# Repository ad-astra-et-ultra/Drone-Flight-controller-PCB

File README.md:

# Drone-Flight-controller-PCB
NodeMCU based flight controller PCB for a drone.

## Schematic

## PCB

## 3D VIEW

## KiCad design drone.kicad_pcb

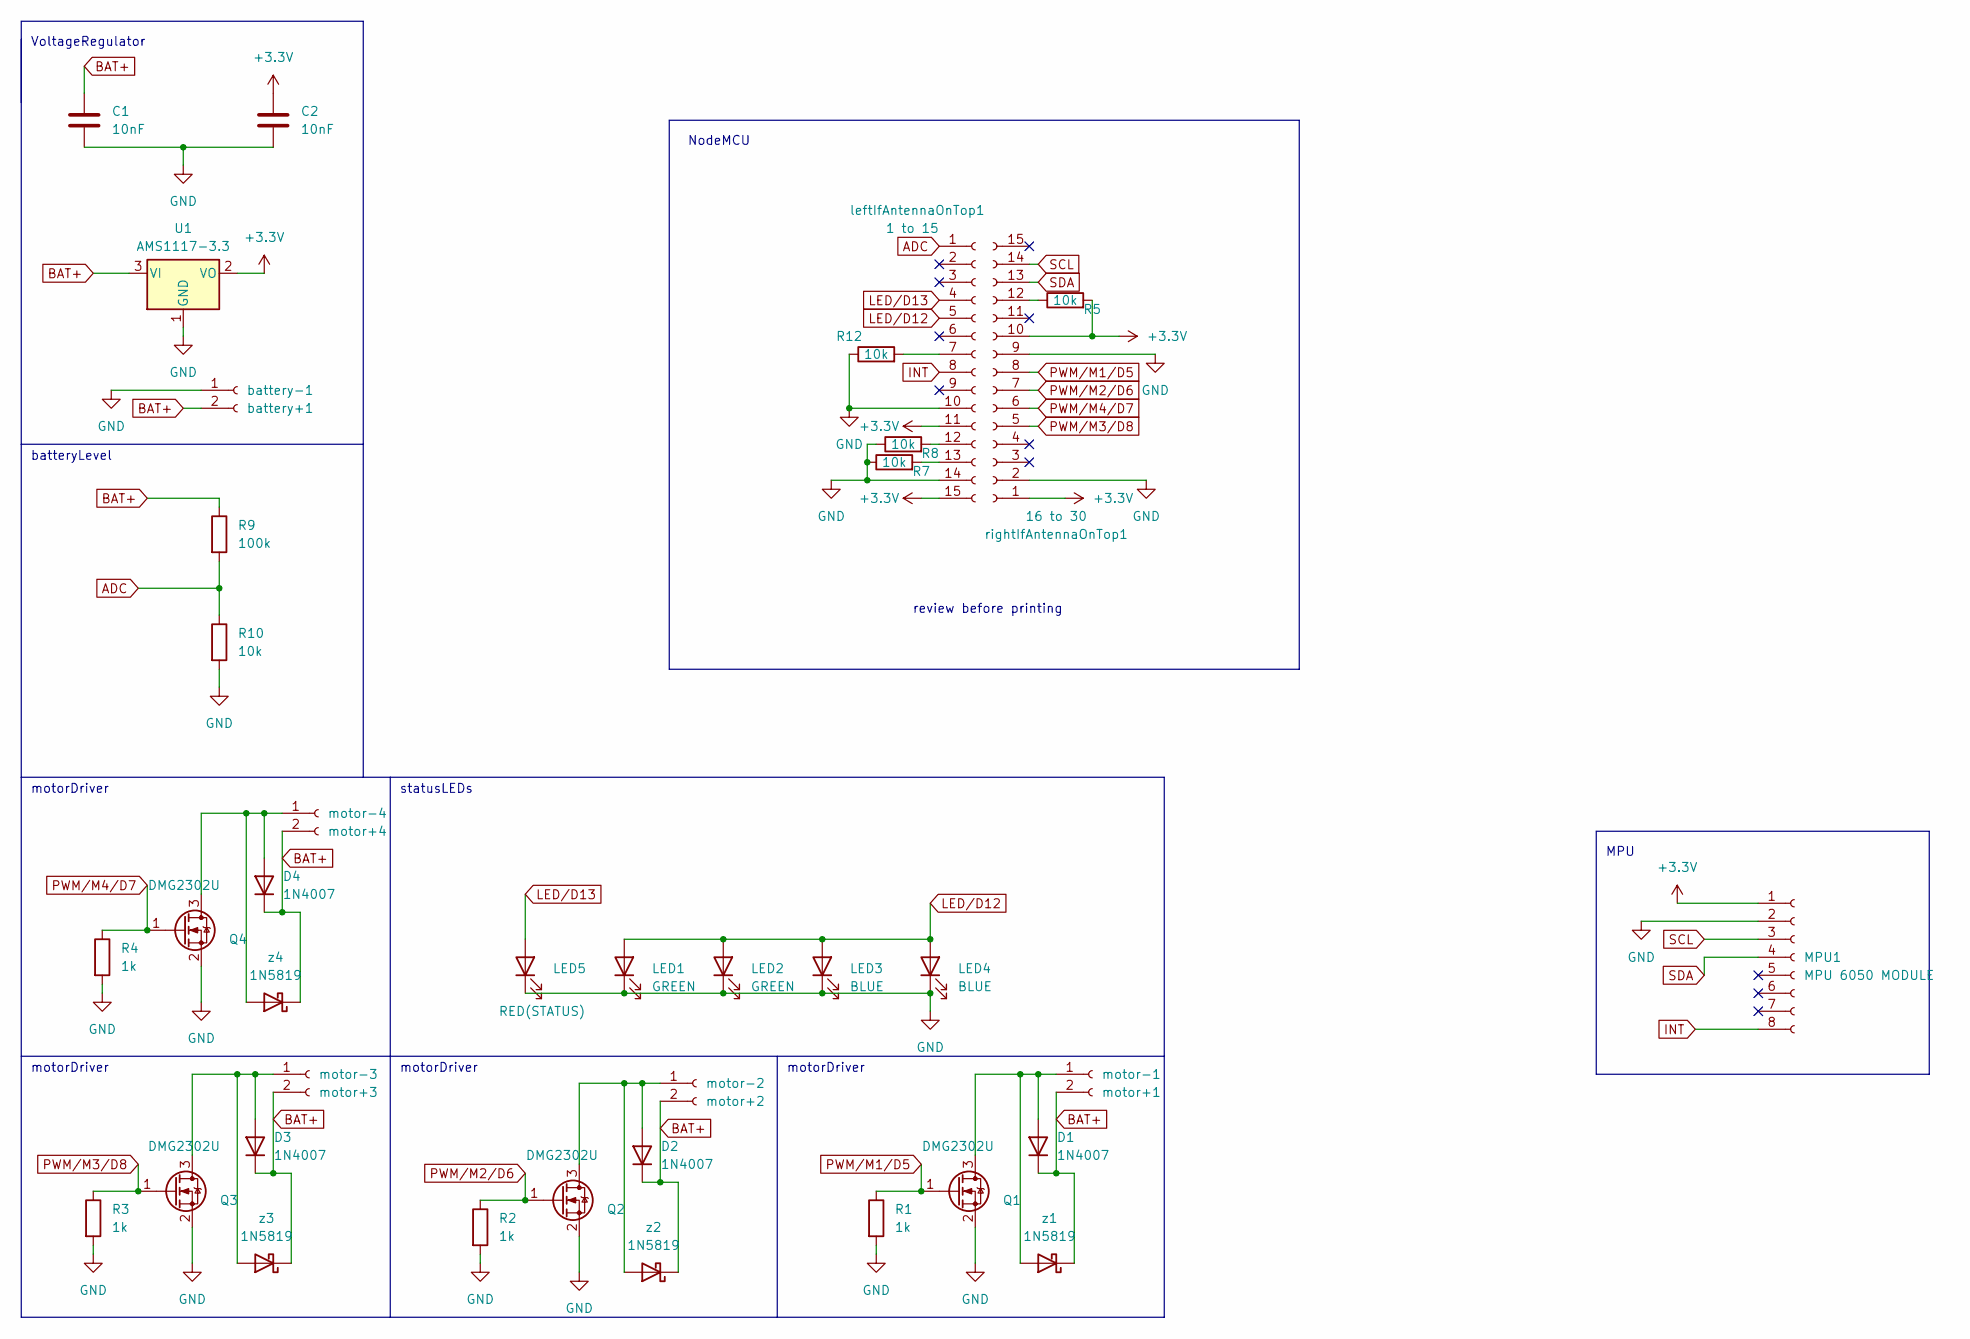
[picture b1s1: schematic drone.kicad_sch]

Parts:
C1, C2: 10nF; C_0201_0603Metric
D1, D2, D3, D4: 1N4007; D_DO-41_SOD81_P10.16mm_Horizontal
LED1, LED2: GREEN; LED_0201_0603Metric
LED3, LED4: BLUE; LED_0201_0603Metric
LED5: RED(STATUS); LED_0201_0603Metric
MPU1: MPU 6050 MODULE; PinSocket_1x08_P2.00mm_Vertical
Q1, Q2, Q3, Q4: DMG2302U; SOT-23
R1, R2, R3, R4: 1k; R_0201_0603Metric
R5, R7, R8, R10, R12: 10k; R_0201_0603Metric
R9: 100k; R_0201_0603Metric
U1: AMS1117-3.3; SOT-223-3_TabPin2
battery-1: battery+1; PinSocket_1x02_P2.00mm_Vertical
leftIfAntennaOnTop1: 1 to 15; PinSocket_1x15_P2.00mm_Vertical
motor-1: motor+1; PinSocket_1x02_P2.00mm_Vertical
motor-2: motor+2; PinSocket_1x02_P2.00mm_Vertical
motor-3: motor+3; PinSocket_1x02_P2.00mm_Vertical
motor-4: motor+4; PinSocket_1x02_P2.00mm_Vertical
rightIfAntennaOnTop1: 16 to 30; PinSocket_1x15_P2.00mm_Vertical
z1, z2, z3, z4: 1N5819; D_DO-41_SOD81_P10.16mm_Horizontal

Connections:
+3V3: C2.1, MPU1.1, R5.2, U1.2 (VO), leftIfAntennaOnTop1.11, leftIfAntennaOnTop1.15, rightIfAntennaOnTop1.1, rightIfAntennaOnTop1.10
ADC: R9.2, R10.1, leftIfAntennaOnTop1.1
BAT+: C1.1, D1.1 (K), D2.1 (K), D3.1 (K), D4.1 (K), R9.1, U1.3 (VI), battery-1.2, motor-1.2, motor-2.2, motor-3.2, motor-4.2, z1.1 (K), z2.1 (K), z3.1 (K), z4.1 (K)
GND: C1.2, C2.2, LED1.1 (K), LED2.1 (K), LED3.1 (K), LED4.1 (K), LED5.1 (K), MPU1.2, Q1.2 (S), Q2.2 (S), Q3.2 (S), Q4.2 (S), R1.2, R2.2, R3.2, R4.2, R7.1, R8.1, R10.2, R12.1, U1.1 (GND), battery-1.1, leftIfAntennaOnTop1.10, leftIfAntennaOnTop1.14, rightIfAntennaOnTop1.2, rightIfAntennaOnTop1.9
INT: MPU1.8, leftIfAntennaOnTop1.8
LED/D12: LED1.2 (A), LED2.2 (A), LED3.2 (A), LED4.2 (A), leftIfAntennaOnTop1.5
LED/D13: LED5.2 (A), leftIfAntennaOnTop1.4
unnamed: D2.2 (A), Q2.3 (D), motor-2.1, z2.2 (A)
unnamed: D3.2 (A), Q3.3 (D), motor-3.1, z3.2 (A)
unnamed: D4.2 (A), Q4.3 (D), motor-4.1, z4.2 (A)
unnamed: D1.2 (A), Q1.3 (D), motor-1.1, z1.2 (A)
unnamed: R5.1, rightIfAntennaOnTop1.12
unnamed: R7.2, leftIfAntennaOnTop1.13
unnamed: R8.2, leftIfAntennaOnTop1.12
unnamed: R12.2, leftIfAntennaOnTop1.7
PWM/M1/D5: Q1.1 (G), R1.1, rightIfAntennaOnTop1.8
PWM/M2/D6: Q2.1 (G), R2.1, rightIfAntennaOnTop1.7
PWM/M3/D8: Q3.1 (G), R3.1, rightIfAntennaOnTop1.5
PWM/M4/D7: Q4.1 (G), R4.1, rightIfAntennaOnTop1.6
SCL: MPU1.3, rightIfAntennaOnTop1.14
SDA: MPU1.4, rightIfAntennaOnTop1.13

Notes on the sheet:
review before printing
motorDriver
VoltageRegulator
NodeMCU
statusLEDs
MPU
batteryLevel

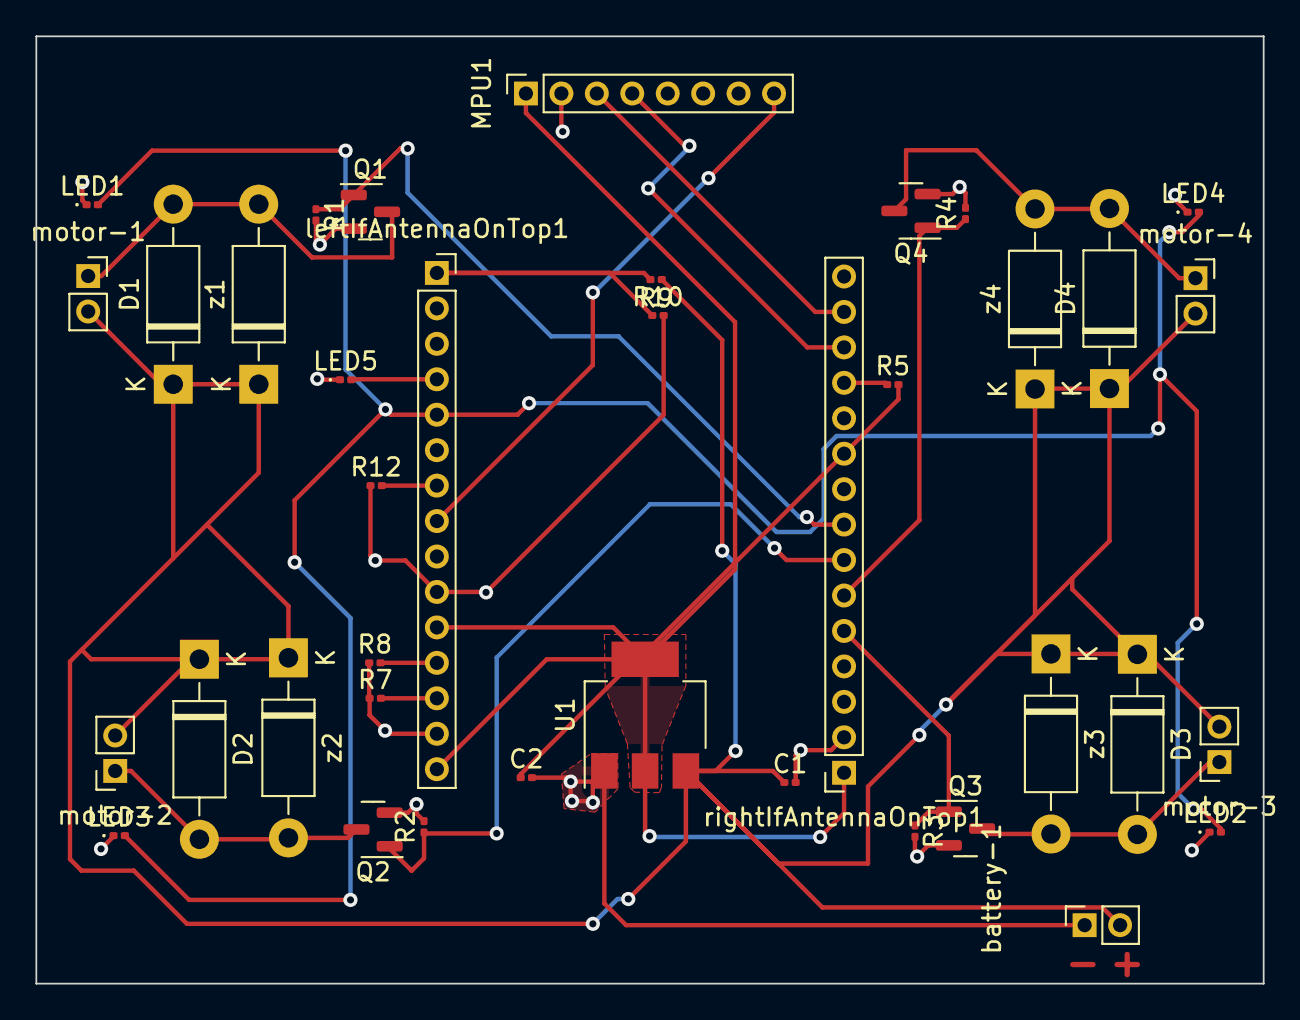
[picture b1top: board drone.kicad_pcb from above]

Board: 2 copper layers, 69.2 x 53.4 mm, 38 parts (0 on the bottom side), 21 nets.

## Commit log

2023-02-28 Create demo
